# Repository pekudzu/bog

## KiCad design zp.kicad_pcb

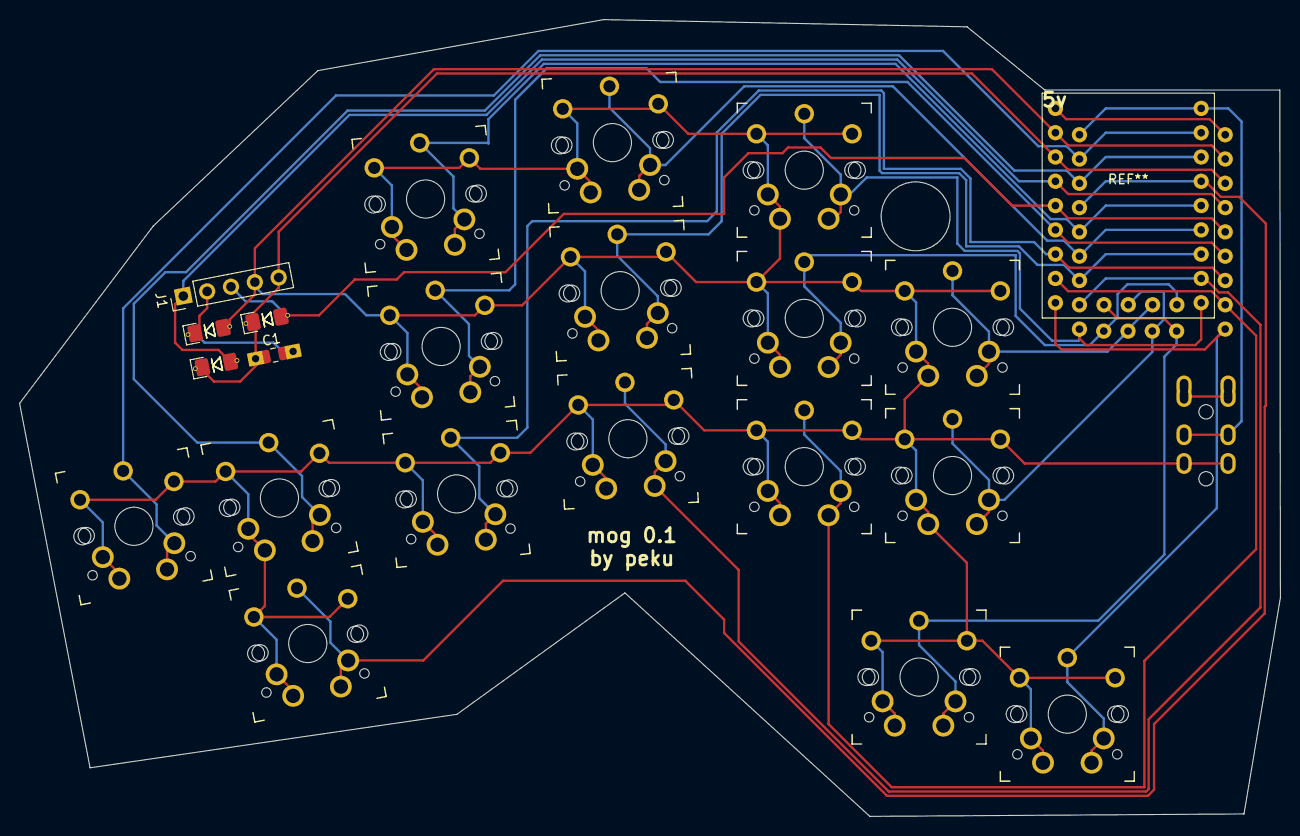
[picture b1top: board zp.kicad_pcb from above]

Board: 2 copper layers, 131.8 x 83.3 mm, 21 parts (0 on the bottom side), 5 nets.

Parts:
C1: 2.2uF; C_THT_SMD_0805_HandSolder_Reversable
J1: TrackPoint; PinHeader_1x05_P2.54mm_Vertical
R1, R2: 4.7kΩ; D_1206_handsolder_reversible
R3: 100kΩ; D_1206_handsolder_reversible
SW1, SW2, SW3, SW4, SW5, SW6, SW7, SW8, SW9, SW10, SW11, SW12, SW13, SW14, SW15, SW16: Choc; SW_MX_choc

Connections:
GND: J1.4, R3.2, SW1.2, SW2.2, SW3.2, SW4.2, SW5.2, SW6.2, SW7.2, SW8.2, SW9.2, SW10.2, SW11.2, SW12.2, SW13.2, SW14.2, SW15.2, SW16.2
unnamed: C1.2, J1.2, R3.1
TP_CLK: J1.3, R1.2
TP_DATA: J1.1, R2.2
VCC: C1.1, J1.5, R1.1, R2.1

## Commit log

2022-06-21 init
